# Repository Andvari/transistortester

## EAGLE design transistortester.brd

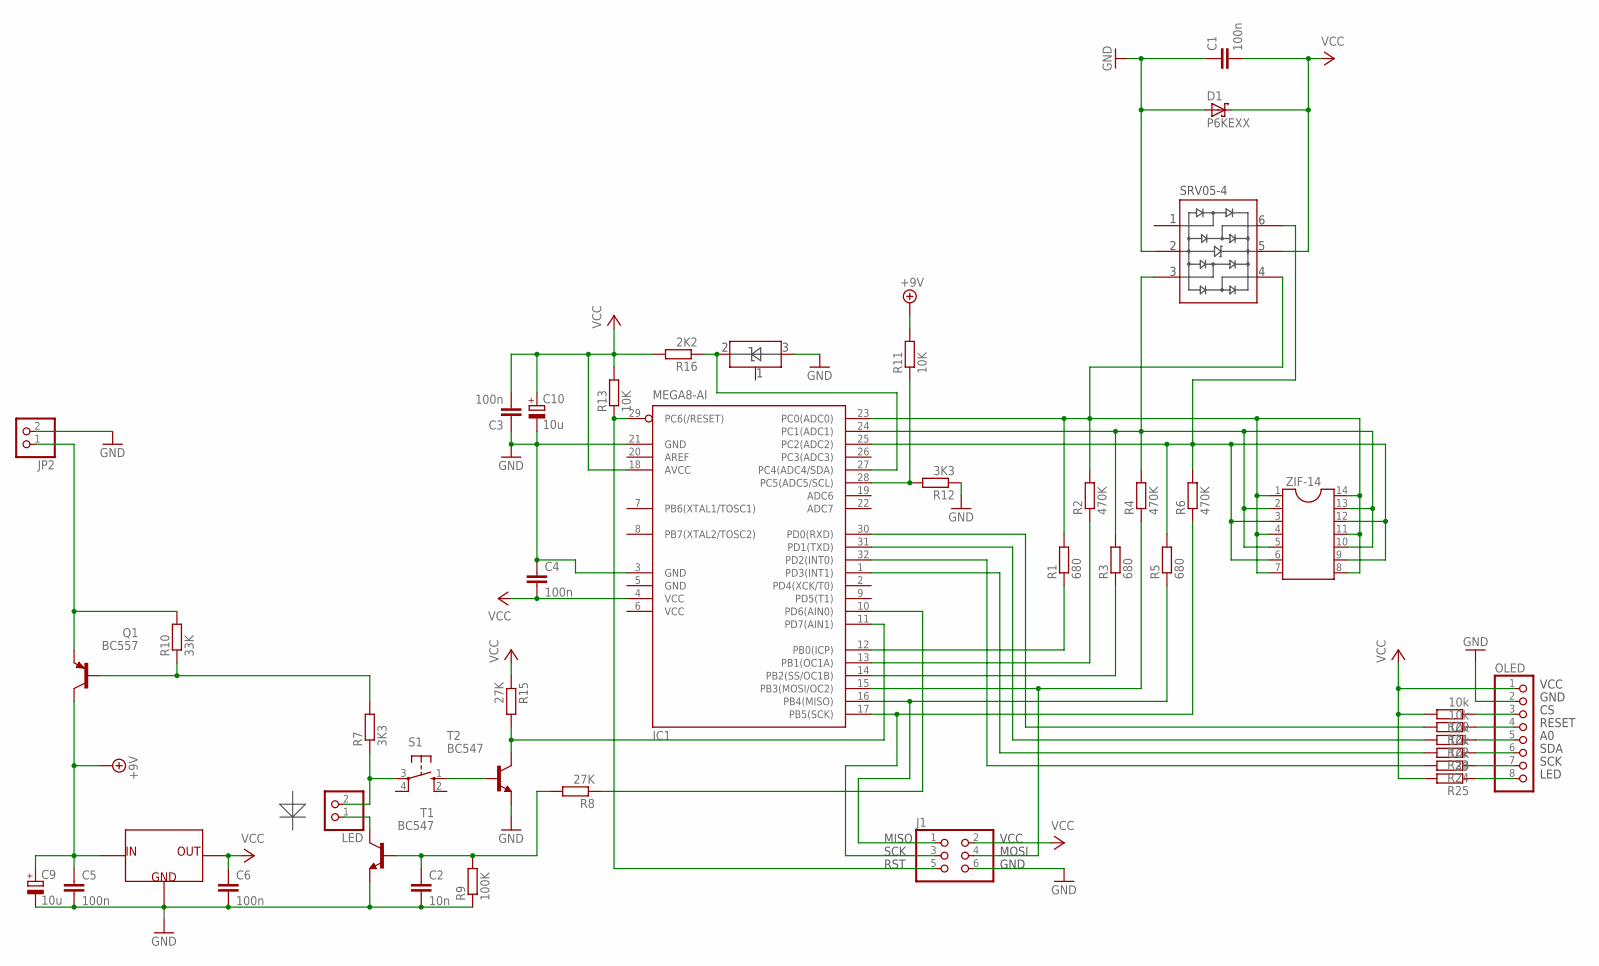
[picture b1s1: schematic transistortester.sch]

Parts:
C1, C3, C4, C5, C6: 100n; C1206
C2: 10n; C1206
C9, C10: 10u; 153CLV-0505
D1: P6KEXX; CB417-15
IC1: MEGA8-AI; TQFP32-08
IC2: MCP1702; TO92-BCE
J1: 2X03
JP2: PINHD-1X2; 1X02
LED: 1X02
OLED: 1X08
Q1: BC557; SOT23-BEC
R1, R3, R5: 680; M1206
R2, R4, R6: 470K; M1206
R7, R12: 3K3; M1206
R8, R15: 27K; M1206
R9: 100K; M1206
R10: 33K; M1206
R11, R13: 10K; M1206
R16: 2K2; M1206
R20, R21, R22, R23, R24: 10k; M1206
R25: 39; M1206
S1: 40-XX; B3F-40XX
T1, T2: BC547; SOT23-BEC
U$2: LM336-TO92; TO92-BCE
U$3: SRV05-4; SOT23-6
ZIF-14: SOCKET-14

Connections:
+9V: C5.1, C9.+, IC2.C, Q1.C, R11.2
GND: C1.1, C3.1, C4.1, C10.-, D1.A, IC1.3 (GND), IC1.5 (GND), IC1.21 (GND), J1.6, JP2.2, OLED.2, R12.1, T2.E, U$2.E, U$3.2
LED: LED.1, T1.C
unnamed: Q1.B, R7.2, R10.1
unnamed: IC1.28 (PC5(ADC5/SCL)), R11.1, R12.2
unnamed: IC1.23 (PC0(ADC0)), R1.2, R2.2, U$3.4, ZIF-14.1, ZIF-14.4, ZIF-14.7, ZIF-14.8, ZIF-14.11, ZIF-14.14
unnamed: IC1.12 (PB0(ICP)), R1.1
unnamed: IC1.11 (PD7(AIN1)), R15.2, T2.C
unnamed: IC1.16 (PB4(MISO)), J1.1, R5.1
unnamed: IC1.13 (PB1(OC1A)), R2.1
unnamed: IC1.15 (PB3(MOSI/OC2)), J1.4, R4.1
unnamed: IC1.17 (PB5(SCK)), J1.3, R6.1
unnamed: IC1.24 (PC1(ADC1)), R3.2, R4.2, U$3.3, ZIF-14.2, ZIF-14.5, ZIF-14.10, ZIF-14.13
unnamed: IC1.14 (PB2(SS/OC1B)), R3.1
unnamed: IC1.10 (PD6(AIN0)), R8.1
unnamed: IC1.27 (PC4(ADC4/SDA)), R16.1, U$2.C
unnamed: S1.1 (S), T2.B
unnamed: LED.2, R7.1, S1.3
unnamed: OLED.8, R25.1
unnamed: C2.1, R8.2, R9.2, T1.B
unnamed: C2.2, C5.2, C6.2, C9.-, IC2.B, R9.1, T1.E
unnamed: OLED.3, R20.1
unnamed: OLED.4, R21.1
unnamed: IC1.30 (PD0(RXD)), R21.2
unnamed: OLED.5, R22.1
unnamed: JP2.1, Q1.E, R10.2
unnamed: IC1.29 (PC6(/RESET)), J1.5, R13.1
unnamed: OLED.6, R23.1
unnamed: OLED.7, R24.1
unnamed: IC1.31 (PD1(TXD)), R22.2
unnamed: IC1.1 (PD3(INT1)), R23.2
unnamed: IC1.32 (PD2(INT0)), R24.2
PROBES: IC1.25 (PC2(ADC2)), R5.2, R6.2, U$3.6, ZIF-14.3, ZIF-14.6, ZIF-14.9, ZIF-14.12
VCC: C1.2, C3.2, C4.2, C6.1, C10.+, D1.C, IC1.4 (VCC), IC1.6 (VCC), IC1.18 (AVCC), IC2.E, J1.2, OLED.1, R13.2, R15.1, R16.2, R20.2, R25.2, U$3.5

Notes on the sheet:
RESET
VCC
GND
MISO
MOSI
SCK
RST
SDA
LED

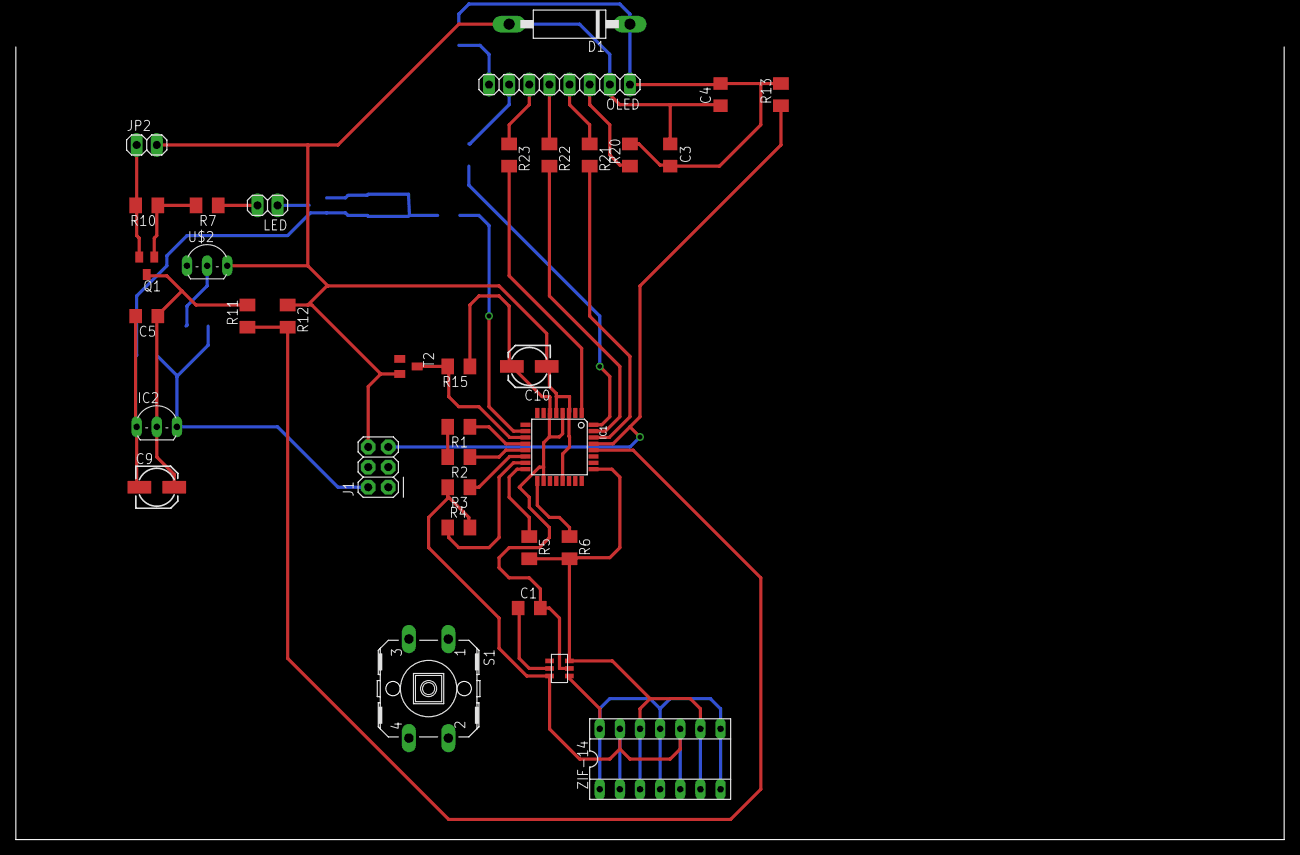
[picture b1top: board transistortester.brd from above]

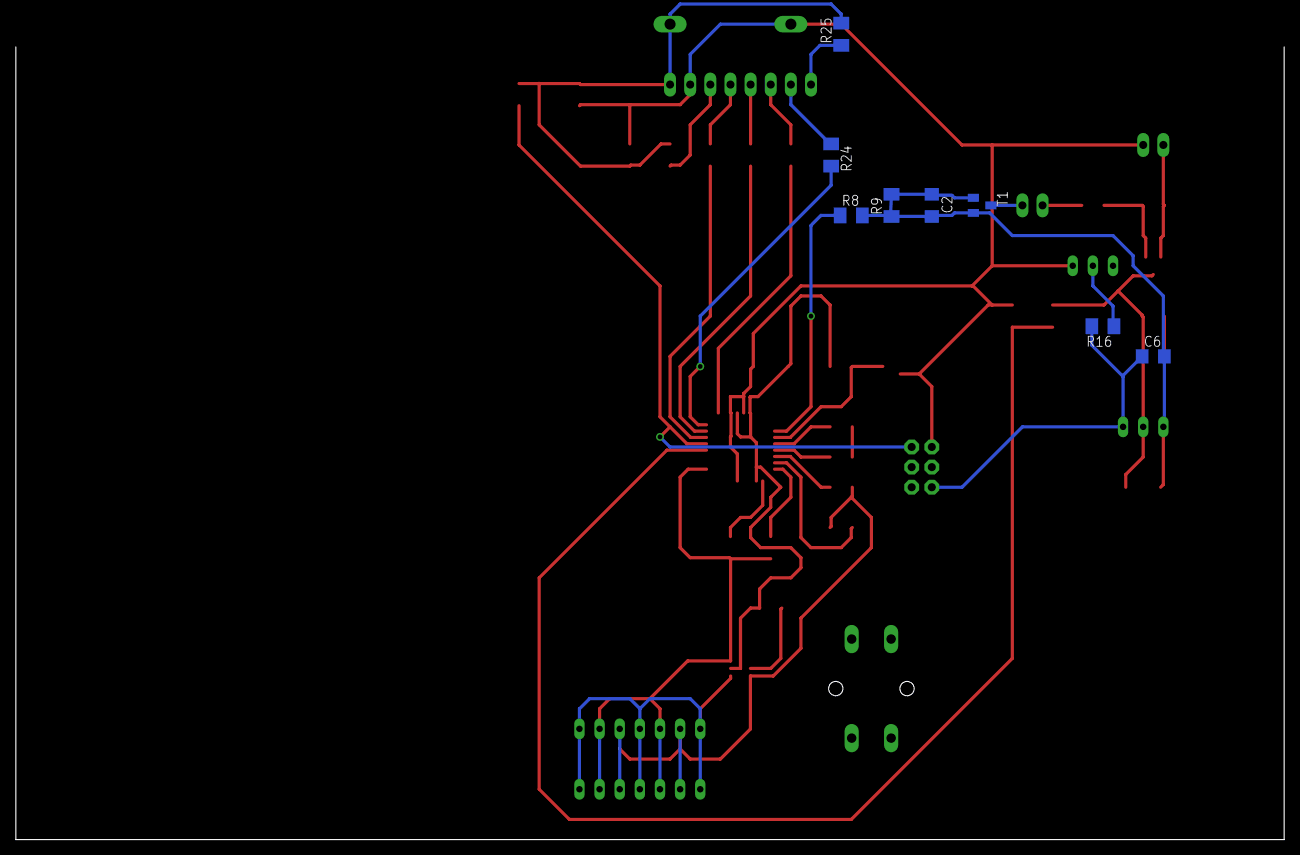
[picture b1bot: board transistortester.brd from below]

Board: 2 copper layers, 160.0 x 100.0 mm, 43 parts (8 on the bottom side), 34 nets.

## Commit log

2018-04-07 Bug fixes

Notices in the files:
parts and their libraries:
SparkFun-Connectors: Licensing: Creative Commons ShareAlike 4.0 International - https://creativecommons.org/licenses/by-sa/4.0
